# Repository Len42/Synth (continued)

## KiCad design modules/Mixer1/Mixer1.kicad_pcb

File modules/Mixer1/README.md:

# Mixer1

## 4HP Eurorack Module

_Half of a [Mixer2](../Mixer2)_

### Features
- 3 -> 1 mixer
- Can be used with CV or audio signals - the inputs are DC coupled
- Input attenuators and output level control
- LED shows the audio signal level

### Notes
I have used linear potentiometers for the level controls. Audio-taper pots would be better for mixing audio signals, but this mixer is meant to work with both audio and CV signals and I find linear pots to be a better compromise.

An LED indicates when the output exceeds the nominal maximum level for Eurorack audio signals, which is 10 V peak-to-peak (-5 V to +5 V). Audio signals with a greater amplitude than that may cause clipping in some modules.
The bi-colour LED is off when the output level is very low or there is no input connected; green when there is a signal up to about 8 V p-p; yellow(ish) to orange(ish) as the output approaches 10 V p-p; and red above about 10 V p-p. Note that these voltage levels are approximate and the LED gives only a rough indication of whether the audio signal level is in the appropriate range.
For CV signals, the LED is less useful - it lights up only when the mixed output is a positive voltage.

PCB layouts are provided in KiCad and gerber formats. A PCB layout for a drilled front panel (with no labels) is also included.

The PCBs that I used can be ordered from OSH Park. The designs are here:
- [Main board](https://oshpark.com/shared_projects/FVIrCDbp)
- [Controls board](https://oshpark.com/shared_projects/FXSeCMCY)
- [Front panel](https://oshpark.com/shared_projects/4AgzBjE7)

Please note that I am a hobbyist, not a trained electronics engineer. No guarantees!

### Software Used

* [KiCad](https://www.kicad.org/) 6.0.9

<hr /><div><div style="float:left; padding-right:10px;"></div><div style="xfloat:left; padding-left:10px;"><br />© 2022 Len Popp CC BY<br />This work is licensed under a <a rel="license" href="http://creativecommons.org/licenses/by/4.0/">Creative Commons Attribution 4.0 International License</a>.</div></div>

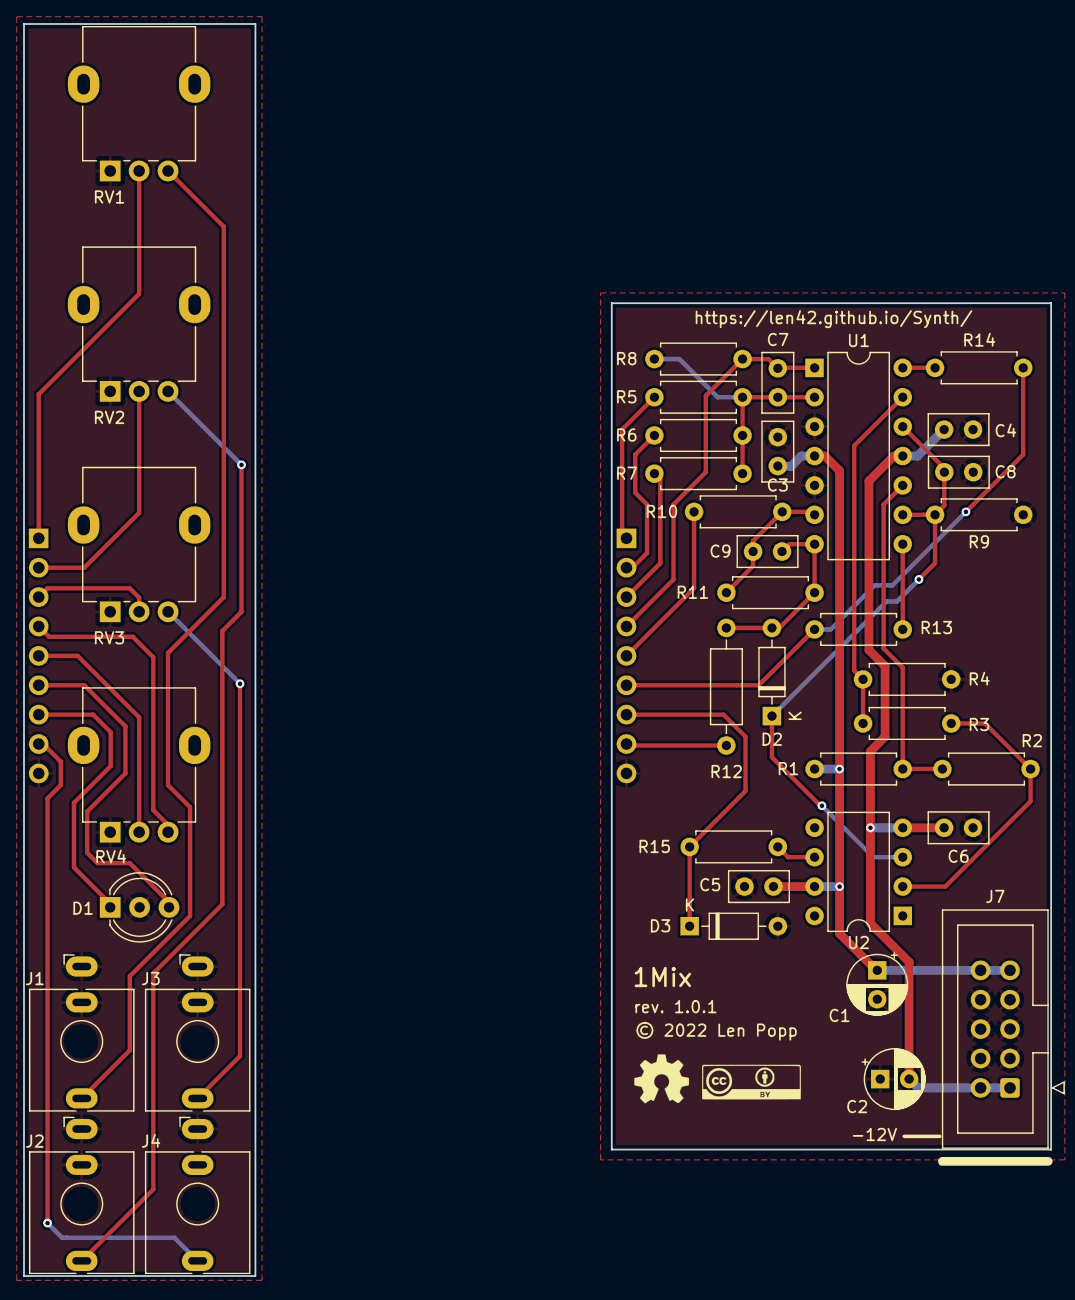
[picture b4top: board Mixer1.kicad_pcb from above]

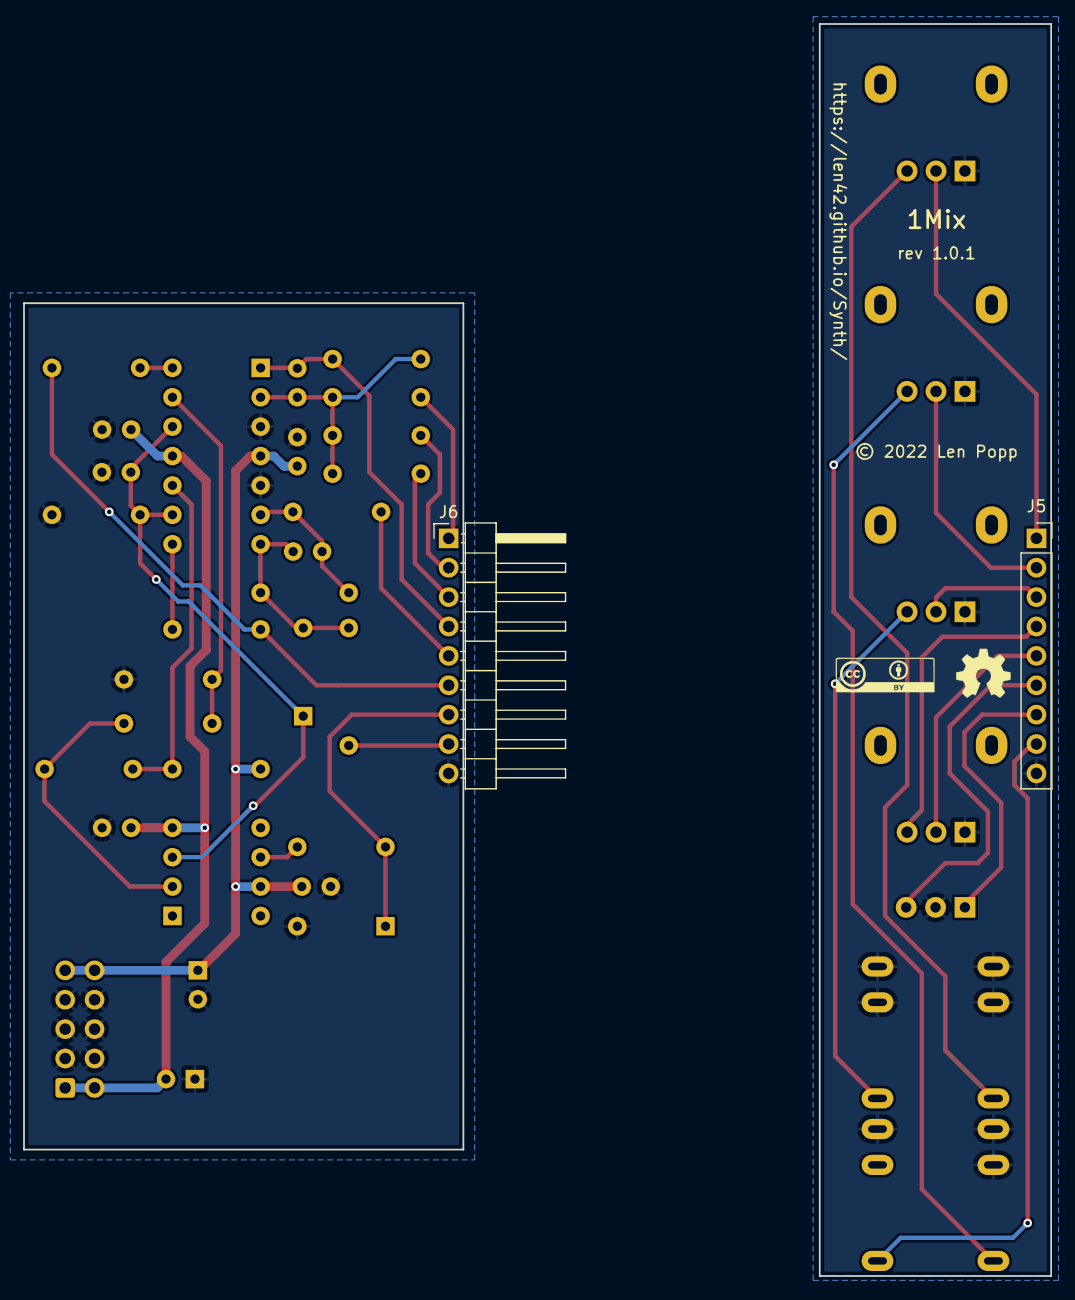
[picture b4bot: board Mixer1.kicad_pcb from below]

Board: 2 copper layers, 88.8 x 108.2 mm, 44 parts (4 on the bottom side), 24 nets.

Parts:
C1, C2: 10U; CP_Radial_D5.0mm_P2.50mm
C3, C4, C5, C6, C8: 100N; C_Disc_D5.0mm_W2.5mm_P2.50mm
C7, C9: 5P6; C_Disc_D5.0mm_W2.5mm_P2.50mm
D1: LED_Dual_5mm_ACA; LED_D5.0mm-3
D2, D3: 1N4148; D_DO-35_SOD27_P7.62mm_Horizontal
G1, G2: Logo_CC_BY
G3, G4: Logo_OSHW
J1, J2, J3, J4: WQP-PJ398; Jack_3.5mm_QingPu_WQP-PJ398SM_Vertical
J5: Conn_PCB_Front; PinSocket_1x09_P2.54mm_Vertical
J6: Conn_PCB_Back; PinHeader_1x09_P2.54mm_Horizontal
J7: Conn_Eurorack_10; IDC-Header-Eurorack-10-TH
R1: 75K; R_Axial_DIN0207_L6.3mm_D2.5mm_P7.62mm_Horizontal
R2: 11K; R_Axial_DIN0207_L6.3mm_D2.5mm_P7.62mm_Horizontal
R3: 36K; R_Axial_DIN0207_L6.3mm_D2.5mm_P7.62mm_Horizontal
R4: 200R; R_Axial_DIN0207_L6.3mm_D2.5mm_P7.62mm_Horizontal
R5, R6, R7, R8, R9, R10, R11: 100K; R_Axial_DIN0207_L6.3mm_D2.5mm_P7.62mm_Horizontal
R12: 51R; R_Axial_DIN0207_L6.3mm_D2.5mm_P10.16mm_Horizontal
R13, R14: 10K; R_Axial_DIN0207_L6.3mm_D2.5mm_P7.62mm_Horizontal
R15: 4K7; R_Axial_DIN0207_L6.3mm_D2.5mm_P7.62mm_Horizontal
RV1, RV2, RV3, RV4: 100K; Potentiometer_Alpha_RD901F-40-00D_Single_Vertical
U1: TL074; DIP-14_W7.62mm
U2: TL071; DIP-8_W7.62mm

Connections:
+12V: C1.1, C3.1, C5.1, J7.9 (+12V), J7.10, R1.1, U1.4 (V+), U2.7 (V+)
-12V: C2.2, C4.2, C6.2, J7.1 (-12V), J7.2, U1.11 (V-), U2.4 (V-)
GAIN: C7.2, J5.4, J6.4, R8.2, RV4.3, U1.1
GAIN-ATTEN: J5.5, J6.5, R10.1, RV4.2
GND: C1.2, C2.1, C3.2, C4.1, C5.2, C6.1, C8.2, D1.2 (K), D3.2 (A), J1.S, J1.TN, J2.S, J2.TN, J3.S, J3.TN, J4.S, J5.9, J6.9, J7.3 (GND), J7.4, J7.5 (GND), J7.6, J7.7 (GND), J7.8, R4.2, R9.1, RV1.1, RV2.1, RV3.1, RV4.1, U1.3 (+), U1.5 (+)
IN-1: J1.T, RV1.3
IN-2: J2.T, RV2.3
IN-3: J3.T, RV3.3
IN-ATTEN-1: J5.1, J6.1, R5.1, RV1.2
IN-ATTEN-2: J5.2, J6.2, R6.1, RV2.2
IN-ATTEN-3: J5.3, J6.3, R7.1, RV3.2
LED-GREEN: D1.3 (A2), J5.6, J6.6, R13.2, R14.2
LED-RED: D1.1 (A1), D3.1 (K), J5.7, J6.7, R15.2
unnamed: C7.1, R5.2, R6.2, R7.2, R8.1, U1.2 (-)
unnamed: C8.1, D2.1 (K), R9.2, U1.9 (-), U1.12 (+), U2.3 (+)
unnamed: C9.1, R10.2, R11.1, U1.6 (-)
unnamed: C9.2, D2.2 (A), R11.2, R12.1, U1.7
unnamed: R13.1, U1.8
unnamed: R14.1, U1.14
unnamed: R15.1, U2.6
OUT: J4.T, J5.8, J6.8, R12.2
VREF-4: R2.2, R3.1, U2.2 (-)
VREF-5: R1.2, R2.1, U1.10 (+)
VREF-LO: R3.2, R4.1, U1.13 (-)

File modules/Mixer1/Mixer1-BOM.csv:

Ref,Qty,Value,Value2,Note,Description,Datasheet,Manufacturer,ManuPartNum,Distributor1,DistributorPartNum1,DistributorPartLink1,Distributor2,DistributorPartNum2,DistributorPartLink2,Distributor3,DistributorPartNum3,DistributorPartLink3
"A1","1","Cable_Eurorack_10","","Length as required","Eurorack 16-10 pin power cable","","","","Thonk","","https://www.thonk.co.uk/shop/eurorack-power-cables/","SynthCube","","https://synthcube.com/cart/eurorack-ribbon-power-cables","Modular Addict","","https://modularaddict.com/parts/eurorack-power-cables-1"
"C1 C2","2","10U","","12 V decoupling","Capacitor - Electrolytic - 12 V decoupling","https://www.mouser.ca/datasheet/2/315/ABA0000C1059-947582.pdf","Panasonic","ECE-A1VKS100I","Mouser","667-ECE-A1VKS100I","https://www.mouser.ca/ProductDetail/667-ECE-A1VKS100I","Thonk","Group_Eurorack_DIY_Essential","https://www.thonk.co.uk/shop/eurorack-diy-essentials/","","",""
"C3 C4 C5 C6 C8","5","100N","","IC decoupling","Capacitor - Ceramic - IC decoupling","https://product.tdk.com/system/files/dam/doc/product/capacit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","TDK","FG18X7R1H104KNT06","Mouser","810-FG18X7R1H104KNT6","https://www.mouser.ca/ProductDetail/810-FG18X7R1H104KNT6","","","","","",""
"C7 C9","2","5P6","C0G/NP0","","Capacitor - Ceramic","https://www.mouser.ca/datasheet/2/212/KEM_C1049_GOLDMAX_C0G-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","KEMET","C315C569D1G5TA","Mouser","80-C315C569D1G","https://www.mouser.ca/ProductDetail/?qs=qe%2F8UmbcoTBh6wC284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","","","","","",""
"D1","1","LED_Dual_5mm_ACA","","","Dual LED, red and green, common cathode on pin 2","https://www.mouser.ca/datasheet/2/216/WP59SURKCGKW-78112.pdf","Kingbright","WP59SURKCGKW","Mouser","604-WP59SURKCGKW","https://www.mouser.ca/ProductDetail/Kingbright/WP59SURKCGKW?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","","","","","",""
"D2 D3","2","1N4148","","","Switching diode, 100V 0.15A, DO-35","https://www.mouser.ca/datasheet/2/308/1N914_D-2309448.pdf","On Semi / Fairchild","1N4148-T50R","Mouser","512-1N4148T50R","https://www.mouser.ca/ProductDetail/?qs=0lQeLiL1qyZS6rosZp7E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","","","","","",""
"J1 J2 J3 J4","4","WQP-PJ398","","","Audio Jack, 2 Poles (Mono / TS), Switched T Pole (Normalling), QingPu / Thonkiconn","http://www.qingpu-electronics.com/en/products/WQP-PJ398SM-362.html","QingPu / Thonk","PJ398SM / WQP518MA","Thonk","PJ398SM","https://www.thonk.co.uk/shop/thonkiconn/","SynthCube","WQP518MA","https://synthcube.com/cart/3-5mm-euro-jacks","Adafruit","4031","https://www.adafruit.com/product/4031"
"J5","1","Conn_PCB_Front","","","Generic connector, single row, 01x09, script generated (kicad-library-utils/schlib/autogen/connector/)","","","","Adafruit","598","https://www.adafruit.com/product/598","Mouser","710-61303211821","https://www.mouser.ca/ProductDetail/Wurth-Elektronik/6130321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","","",""
"J6","1","Conn_PCB_Back","","","Generic connector, single row, 01x09, script generated (kicad-library-utils/schlib/autogen/connector/)","","","","Adafruit","392","https://www.adafruit.com/product/392","Mouser","649-1012937893601BLF","https://www.mouser.ca/ProductDetail/649-1012937893601BLF","","",""
"J7","1","Conn_Eurorack_10","","","Eurorack 10-pin board power connector","https://www.mouser.ca/datasheet/2/445/61201021621-1717731.pdf","Wurth Elektronik","61201021621","Mouser","710-61201021621","https://www.mouser.ca/ProductDetail/Wurth-Elektronik/6120102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","Thonk","523-G821EU210AAL10Y","https://www.thonk.co.uk/shop/eurorack-diy-essentials/","","",""
"R1","1","75K","1%, 1/6 W","","Resistor","https://www.mouser.ca/datasheet/2/447/Yageo_LR_MFR_1-1714151.pdf","YAGEO","MFR-12FTF52-75K","Mouser","603-MFR-12FTF52-75K","https://www.mouser.ca/ProductDetail/YAGEO/MFR-12FTF52-75K?qs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","","","","","",""
"R2","1","11K","1%, 1/6 W","","Resistor","https://www.mouser.ca/datasheet/2/447/Yageo_LR_MFR_1-1714151.pdf","YAGEO","MFR-12FTF52-11K","Mouser","603-MFR-12FTF52-11K","https://www.mouser.ca/ProductDetail/YAGEO/MFR-12FTF52-11K?qs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","","","","","",""
"R3","1","36K","1%, 1/6 W","","Resistor","https://www.mouser.ca/datasheet/2/447/Yageo_LR_MFR_1-1714151.pdf","YAGEO","MFR-12FTF52-36K","Mouser","603-MFR-12FTF52-36K","https://www.mouser.ca/ProductDetail/YAGEO/MFR-12FTF52-36K?qs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","","","","","",""
"R4","1","200R","1%, 1/6 W","","Resistor","https://www.mouser.ca/datasheet/2/447/Yageo_LR_MFR_1-1714151.pdf","YAGEO","MFR-12FTF52-200R","Mouser","603-MFR-12FTF52-200R","https://www.mouser.ca/ProductDetail/603-MFR-12FTF52-200R","","","","","",""
"R5 R6 R7 R8 R9 R10 R11","7","100K","1%, 1/6 W","","Resistor","https://www.mouser.ca/datasheet/2/447/Yageo_LR_MFR_1-1714151.pdf","YAGEO","MFR-12FTF52-100K","Mouser","603-MFR-12FTF52-100K","https://www.mouser.ca/ProductDetail/YAGEO/MFR-12FTF52-100K?q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","","","","","",""
"R12","1","51R","5%, 1/4 W","Output limiting","Resistor","https://www.mouser.ca/datasheet/2/447/Yageo_LR_MFR_1-1714151.pdf","YAGEO","MFR-25FBF52-51R","Mouser","603-MFR-25FBF52-51R","https://www.mouser.ca/ProductDetail/?qs=oAGoVhmvjhzVx2bdEH1T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","","","","","",""
"R13 R14","2","10K","1%, 1/6 W","","Resistor","https://www.mouser.ca/datasheet/2/447/Yageo_LR_MFR_1-1714151.pdf","YAGEO","MFR-12FTF52-10K","Mouser","603-MFR-12FTF52-10K","https://www.mouser.ca/ProductDetail/YAGEO/MFR-12FTF52-10K?qs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","","","","","",""
"R15","1","4K7","1%, 1/6 W","","Resistor","https://www.mouser.ca/datasheet/2/447/Yageo_LR_MFR_1-1714151.pdf","YAGEO","MFR-12FTF52-4K7","Mouser","603-MFR-12FTF52-4K7","https://www.mouser.ca/ProductDetail/YAGEO/MFR-12FTF52-4K7?qs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","","","","","",""
"RV1 RV2 RV3 RV4","4","100K","LIN","","Potentiometer","https://www.mouser.ca/datasheet/2/13/alpha_taiwan_08192019_R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","Alpha","RD901F-*","Thonk","Group_Pot_Alpha_6.35mm","https://www.thonk.co.uk/shop/alpha-9mm-pots/","Mouser","311-1940F-*","https://www.mouser.ca/c/passive-components/potentiometers-tr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","SynthCube","9MMALPHAPOTMSTR","https://synthcube.com/cart/alpha-9mm-potentiometer-right-ang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"
"U1","1","TL074","","","Quad Low-Noise JFET-Input Operational Amplifiers, DIP-14/SOIC-14","http://www.ti.com/lit/ds/symlink/tl071.pdf","Texas Instruments","TL074BCN","Mouser","595-TL074BCN","https://www.mouser.ca/ProductDetail/?qs=vxEfx8VrU7BHurOY5iQd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","","","","","",""
"U2","1","TL071","","","Single Low-Noise JFET-Input Operational Amplifiers, DIP-8/SOIC-8","http://www.ti.com/lit/ds/symlink/tl071.pdf","Texas Instruments","TL071BCP","Digi-Key","296-34258-5-ND","https://www.digikey.ca/en/products/detail/texas-instruments/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","Mouser","595-TL071IPE4","https://www.mouser.ca/ProductDetail/Texas-Instruments/TL071I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","","",""

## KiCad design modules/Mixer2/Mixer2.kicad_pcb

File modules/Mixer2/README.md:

# Dual Mixer

## 8HP Eurorack Module

### Features
- Two 3-channel mixers
- Can be used with CV or audio signals - the inputs are DC coupled
- Input attenuators and output level controls
- When output 1 is unplugged it's normalled to mix into output 2, making a 6-channel mixer
- LEDs show the audio signal level

### Notes
I have used linear potentiometers for the level controls. Audio-taper pots would be better for mixing audio signals, but this mixer is meant to work with both audio and CV signals and I find linear pots to be a better compromise.

LEDs are used to indicate when an output exceeds the nominal maximum level for Eurorack audio signals, which is 10 V peak-to-peak (-5 V to +5 V). Audio signals with a greater amplitude than that may cause clipping in some modules.
The bi-colour LEDs (one for each output) are off when the output level is very low or there is no input connected; green when there is a signal up to about 8 V p-p; yellow(ish) to orange(ish) as the output approaches 10 V p-p; and red above about 10 V p-p. Note that these voltage levels are approximate and the LEDs give only a rough indication of whether the audio signal level is in the appropriate range.
For CV signals, the LEDs are less useful - they light up only when the mixed output is a positive voltage.

PCB layouts are provided in KiCad and gerber formats. A drilling template is provided for the front panel.

The PCBs that I used can be ordered from OSH Park. The designs are here:
- [Main board](https://oshpark.com/shared_projects/YErYkHA9)
- [Controls board](https://oshpark.com/shared_projects/AXUIl19Y)

Please note that I am a hobbyist, not a trained electronics engineer. No guarantees!

### Software Used

* [KiCad](https://www.kicad.org/) 6.0.6

<hr /><div><div style="float:left; padding-right:10px;"></div><div style="xfloat:left; padding-left:10px;"><br />© 2022 Len Popp CC BY<br />This work is licensed under a <a rel="license" href="http://creativecommons.org/licenses/by/4.0/">Creative Commons Attribution 4.0 International License</a>.</div></div>

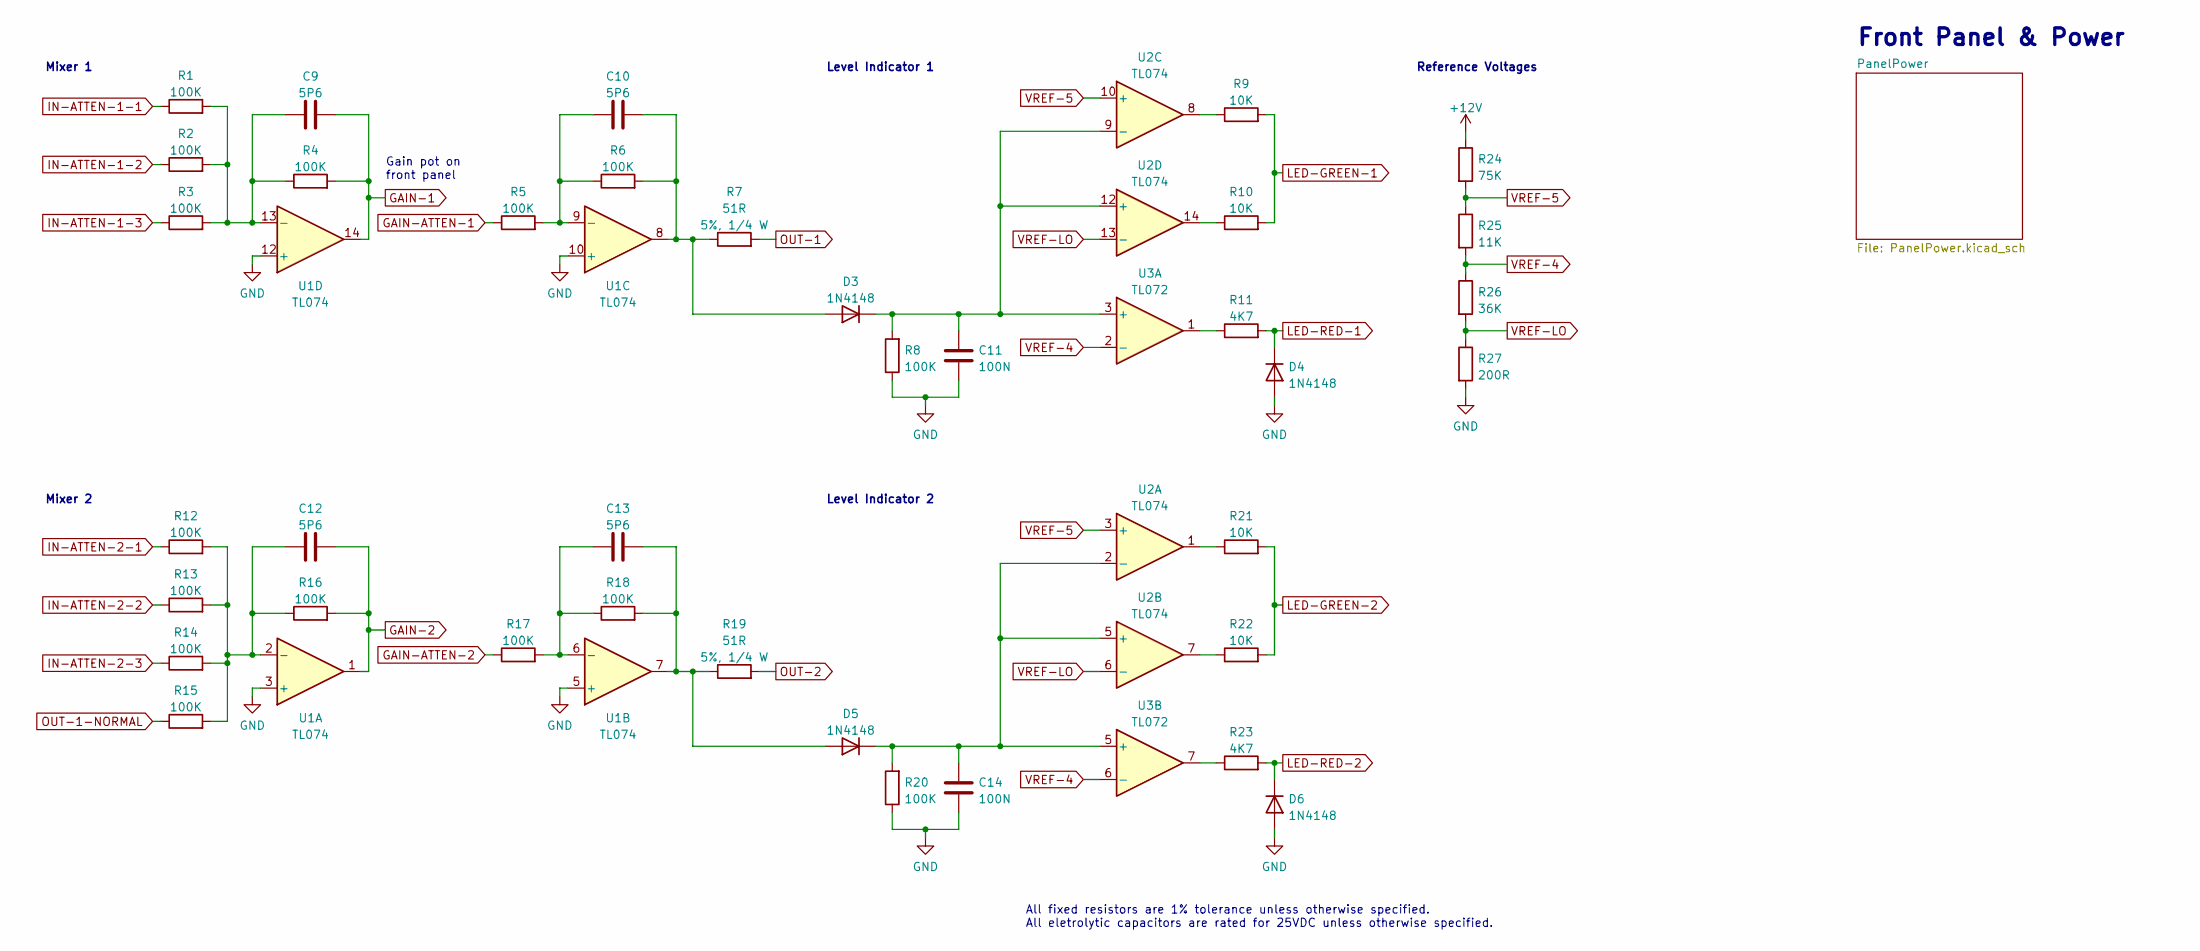
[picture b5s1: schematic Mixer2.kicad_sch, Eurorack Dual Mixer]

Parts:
C9, C10, C12, C13: 5P6; C_Disc_D5.0mm_W2.5mm_P2.50mm; ManufacturerPartNum C315C569D1G5TA
C11, C14: 100N; C_Disc_D5.0mm_W2.5mm_P2.50mm; ManufacturerPartNum FG18X7R1H104KNT06
D3, D4, D5, D6: 1N4148; D_DO-35_SOD27_P7.62mm_Horizontal; ManufacturerPartNum 1N4148-T50R
R1, R2, R3, R4, R5, R6, R8, R12, R13, R14, R15, R16, R17, R18, R20: 100K; R_Axial_DIN0207_L6.3mm_D2.5mm_P7.62mm_Horizontal; ManufacturerPartNum MFR-12FTF52-100K
R7, R19: 51R; R_Axial_DIN0207_L6.3mm_D2.5mm_P10.16mm_Horizontal; ManufacturerPartNum MFR-25FBF52-51R
R9, R10, R21, R22: 10K; R_Axial_DIN0207_L6.3mm_D2.5mm_P7.62mm_Horizontal; ManufacturerPartNum MFR-12FTF52-10K
R11, R23: 4K7; R_Axial_DIN0207_L6.3mm_D2.5mm_P7.62mm_Horizontal; ManufacturerPartNum MFR-12FTF52-4K7
R24: 75K; R_Axial_DIN0207_L6.3mm_D2.5mm_P7.62mm_Horizontal; ManufacturerPartNum MFR-12FTF52-75K
R25: 11K; R_Axial_DIN0207_L6.3mm_D2.5mm_P7.62mm_Horizontal; ManufacturerPartNum MFR-12FTF52-11K
R26: 36K; R_Axial_DIN0207_L6.3mm_D2.5mm_P7.62mm_Horizontal; ManufacturerPartNum MFR-12FTF52-36K
R27: 200R; R_Axial_DIN0207_L6.3mm_D2.5mm_P7.62mm_Horizontal; ManufacturerPartNum MFR-12FTF52-200R
U1, U2: TL074; DIP-14_W7.62mm; ManufacturerPartNum TL074BCN
U3: TL072; DIP-8_W7.62mm; ManufacturerPartNum TL072BCP

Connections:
+12V: R24.1; also elsewhere on the board
GAIN-1: C9.2, R4.2, U1.14; also elsewhere on the board
GAIN-2: C12.2, R16.2, U1.1; also elsewhere on the board
GAIN-ATTEN-1: R5.1; also elsewhere on the board
GAIN-ATTEN-2: R17.1; also elsewhere on the board
GND: C11.2, C14.2, D4.2 (A), D6.2 (A), R8.1, R20.1, R27.2, U1.3 (+), U1.5 (+), U1.10 (+), U1.12 (+); also elsewhere on the board
IN-ATTEN-1-1: R1.1; also elsewhere on the board
IN-ATTEN-1-2: R2.1; also elsewhere on the board
IN-ATTEN-1-3: R3.1; also elsewhere on the board
IN-ATTEN-2-1: R12.1; also elsewhere on the board
IN-ATTEN-2-2: R13.1; also elsewhere on the board
IN-ATTEN-2-3: R14.1; also elsewhere on the board
LED-GREEN-1: R9.2, R10.2; also elsewhere on the board
LED-GREEN-2: R21.2, R22.2; also elsewhere on the board
LED-RED-1: D4.1 (K), R11.2; also elsewhere on the board
LED-RED-2: D6.1 (K), R23.2; also elsewhere on the board
unnamed: C9.1, R1.2, R2.2, R3.2, R4.1, U1.13 (-)
unnamed: C10.1, R5.2, R6.1, U1.9 (-)
unnamed: C10.2, D3.2 (A), R6.2, R7.1, U1.8
unnamed: C11.1, D3.1 (K), R8.2, U2.9 (-), U2.12 (+), U3.3 (+)
unnamed: C12.1, R12.2, R13.2, R14.2, R15.2, R16.1, U1.2 (-)
unnamed: C13.1, R17.2, R18.1, U1.6 (-)
unnamed: C13.2, D5.2 (A), R18.2, R19.1, U1.7
unnamed: C14.1, D5.1 (K), R20.2, U2.2 (-), U2.5 (+), U3.5 (+)
unnamed: R9.1, U2.8
unnamed: R10.1, U2.14
unnamed: R11.1, U3.1
unnamed: R21.1, U2.1
unnamed: R22.1, U2.7
unnamed: R23.1, U3.7
OUT-1: R7.2; also elsewhere on the board
OUT-1-NORMAL: R15.1; also elsewhere on the board
OUT-2: R19.2; also elsewhere on the board
VREF-4: R25.2, R26.1, U3.2 (-), U3.6 (-)
VREF-5: R24.2, R25.1, U2.3 (+), U2.10 (+)
VREF-LO: R26.2, R27.1, U2.6 (-), U2.13 (-)

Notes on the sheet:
Reference Voltages
All fixed resistors are 1% tolerance unless otherwise specified. All eletrolytic capacitors are rated for 25VDC unless otherwise specified.
Gain pot on front panel
Level Indicator 1
Level Indicator 2
Mixer 1
Mixer 2
Front Panel & Power

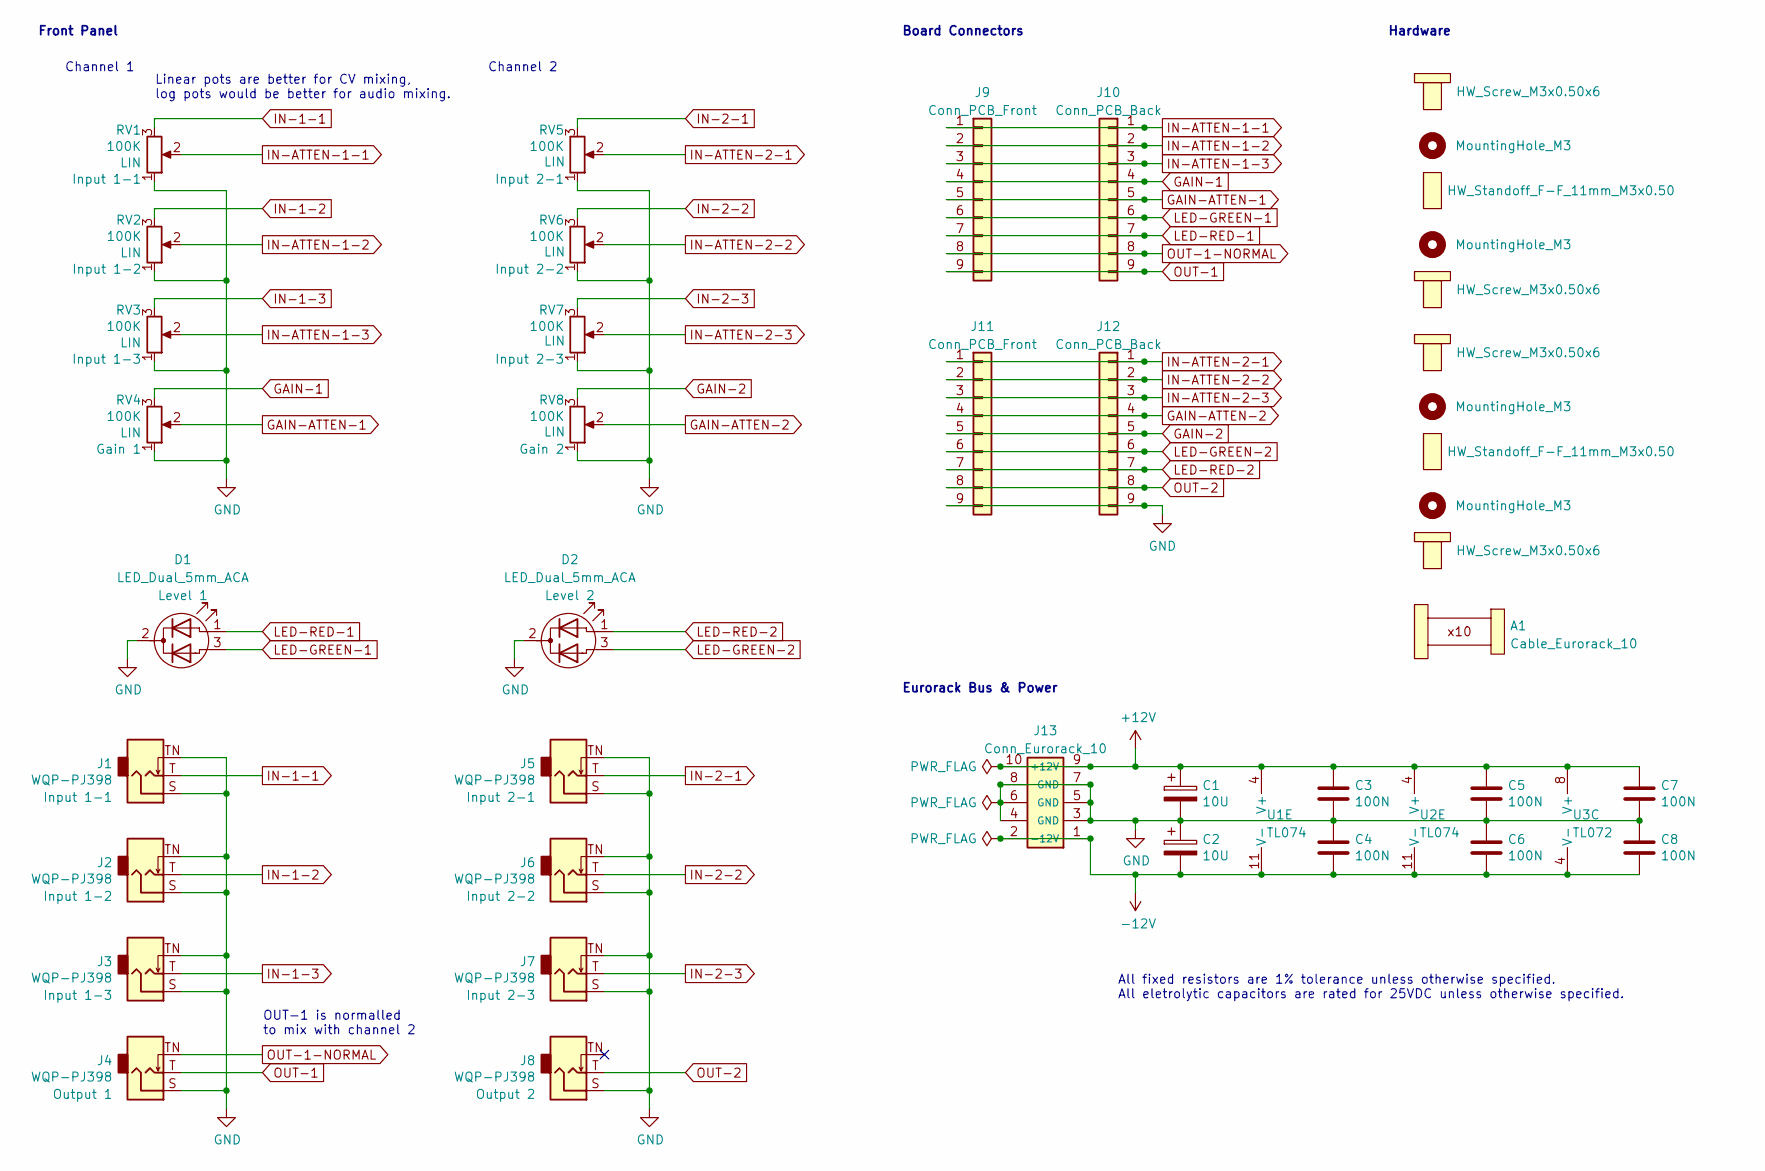
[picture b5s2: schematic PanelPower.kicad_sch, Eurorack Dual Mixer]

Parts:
A1: Cable_Eurorack_10; NoFootprint
C1, C2: 10U; CP_Radial_D5.0mm_P2.50mm; ManufacturerPartNum ECE-A1VKS100I
C3, C4, C5, C6, C7, C8: 100N; C_Disc_D5.0mm_W2.5mm_P2.50mm; ManufacturerPartNum FG18X7R1H104KNT06
D1, D2: LED_Dual_5mm_ACA; LED_D5.0mm-3; ManufacturerPartNum WP59SURKCGKW
H1, H5, H6, H10: HW_Screw_M3x0.50x6
H2, H4, H7, H9: MountingHole_M3; MountingHole_PCB_3.2mm_M3
H3, H8: HW_Standoff_F-F_11mm_M3x0.50; ManufacturerPartNum 05.03.111
J1, J2, J3, J4, J5, J6, J7, J8: WQP-PJ398; Jack_3.5mm_QingPu_WQP-PJ398SM_Vertical; ManufacturerPartNum PJ398SM / WQP518MA
J9, J11: Conn_PCB_Front; PinSocket_1x09_P2.54mm_Vertical
J10, J12: Conn_PCB_Back; PinHeader_1x09_P2.54mm_Vertical
J13: Conn_Eurorack_10; IDC-Header-Eurorack-10-TH; ManufacturerPartNum 61201021621
RV1, RV2, RV3, RV4, RV5, RV6, RV7, RV8: 100K; Potentiometer_Alpha_RD901F-40-00D_Single_Vertical; ManufacturerPartNum RD901F-*
U1, U2: TL074; DIP-14_W7.62mm; ManufacturerPartNum TL074BCN
U3: TL072; DIP-8_W7.62mm; ManufacturerPartNum TL072BCP

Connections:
+12V: C1.1, C3.1, C5.1, C7.1, J13.9 (+12V), J13.10, U1.4 (V+), U2.4 (V+), U3.8 (V+); also elsewhere on the board
-12V: C2.2, C4.2, C6.2, C8.2, J13.1 (-12V), J13.2, U1.11 (V-), U2.11 (V-), U3.4 (V-)
GAIN-1: J9.4, J10.4, RV4.3; also elsewhere on the board
GAIN-2: J11.5, J12.5, RV8.3; also elsewhere on the board
GAIN-ATTEN-1: J9.5, J10.5, RV4.2; also elsewhere on the board
GAIN-ATTEN-2: J11.4, J12.4, RV8.2; also elsewhere on the board
GND: C1.2, C2.1, C3.2, C4.1, C5.2, C6.1, C7.2, C8.1, D1.2 (K), D2.2 (K), J1.S, J1.TN, J2.S, J2.TN, J3.S, J3.TN, J4.S, J5.S, J5.TN, J6.S, J6.TN, J7.S, J7.TN, J8.S, J11.9, J12.9, J13.3 (GND), J13.4, J13.5 (GND), J13.6, J13.7 (GND), J13.8, RV1.1, RV2.1, RV3.1, RV4.1, RV5.1, RV6.1, RV7.1, RV8.1; also elsewhere on the board
IN-1-1: J1.T, RV1.3
IN-1-2: J2.T, RV2.3
IN-1-3: J3.T, RV3.3
IN-2-1: J5.T, RV5.3
IN-2-2: J6.T, RV6.3
IN-2-3: J7.T, RV7.3
IN-ATTEN-1-1: J9.1, J10.1, RV1.2; also elsewhere on the board
IN-ATTEN-1-2: J9.2, J10.2, RV2.2; also elsewhere on the board
IN-ATTEN-1-3: J9.3, J10.3, RV3.2; also elsewhere on the board
IN-ATTEN-2-1: J11.1, J12.1, RV5.2; also elsewhere on the board
IN-ATTEN-2-2: J11.2, J12.2, RV6.2; also elsewhere on the board
IN-ATTEN-2-3: J11.3, J12.3, RV7.2; also elsewhere on the board
LED-GREEN-1: D1.3 (A2), J9.6, J10.6; also elsewhere on the board
LED-GREEN-2: D2.3 (A2), J11.6, J12.6; also elsewhere on the board
LED-RED-1: D1.1 (A1), J9.7, J10.7; also elsewhere on the board
LED-RED-2: D2.1 (A1), J11.7, J12.7; also elsewhere on the board
OUT-1: J4.T, J9.9, J10.9; also elsewhere on the board
OUT-1-NORMAL: J4.TN, J9.8, J10.8; also elsewhere on the board
OUT-2: J8.T, J11.8, J12.8; also elsewhere on the board

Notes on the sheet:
Hardware
All fixed resistors are 1% tolerance unless otherwise specified. All eletrolytic capacitors are rated for 25VDC unless otherwise specified.
Front Panel
Board Connectors
Linear pots are better for CV mixing, log pots would be better for audio mixing.
OUT-1 is normalled to mix with channel 2
Eurorack Bus & Power
Channel 1
Channel 2
